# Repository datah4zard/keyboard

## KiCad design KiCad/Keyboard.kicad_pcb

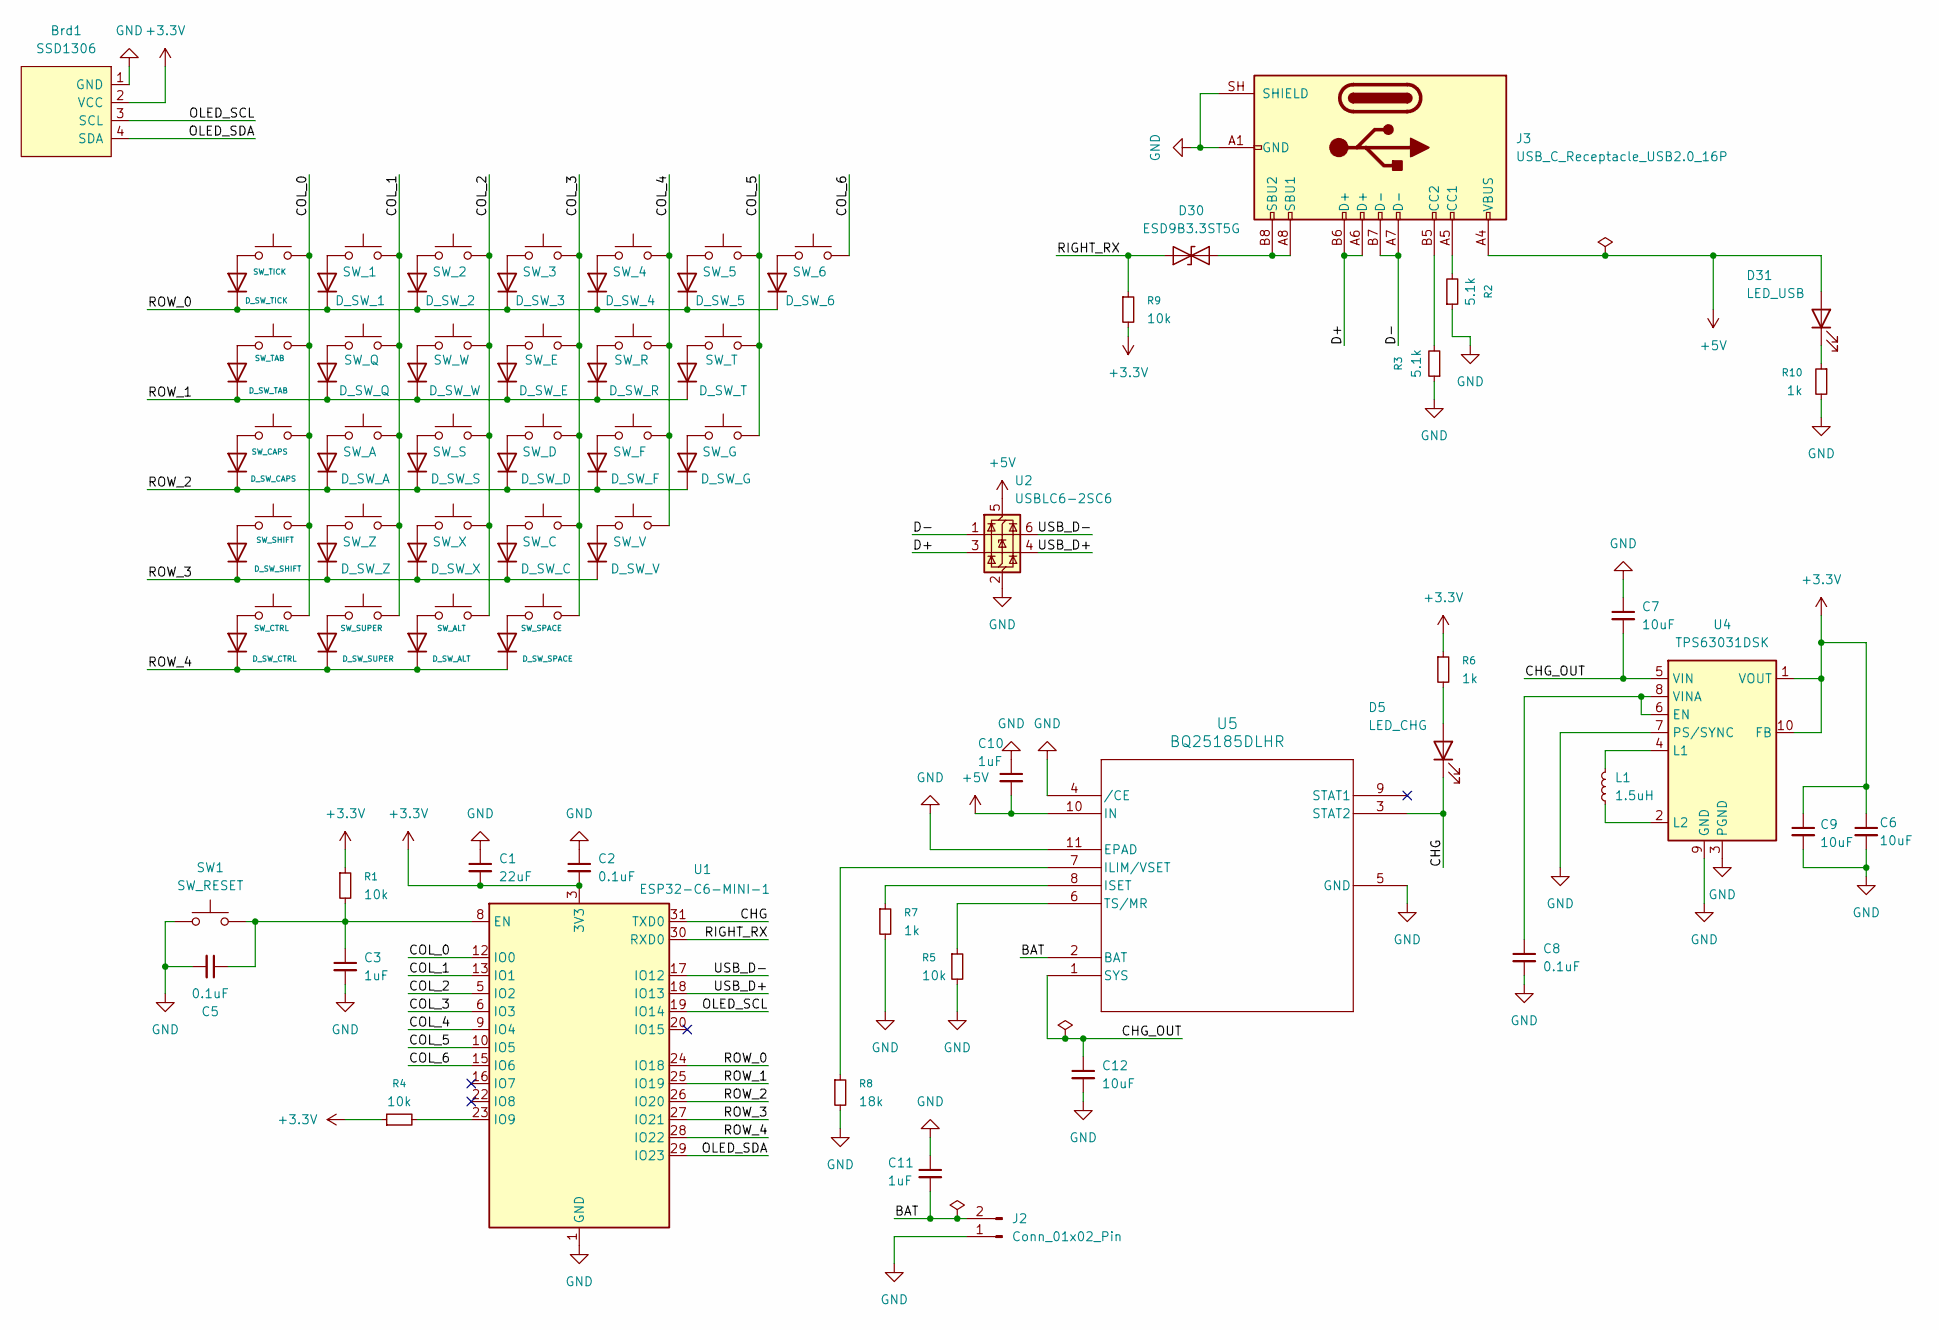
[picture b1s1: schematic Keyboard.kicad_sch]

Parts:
Brd1: SSD1306; 128x64OLED
C1: 22uF; C_0603_1608Metric
C2, C5, C8: 0.1uF; C_0603_1608Metric
C3: 1uF; C_0603_1608Metric
C6, C7, C9: 10uF; C_0603_1608Metric
C10, C11: 1uF; C_0402_1005Metric
C12: 10uF; C_0402_1005Metric
D1: D_SW_TICK; D_SOD-123
D2: D_SW_TAB; D_SOD-123
D3: D_SW_CAPS; D_SOD-123
D4: D_SW_SHIFT; D_SOD-123
D5: LED_CHG; LED_0805_2012Metric
D6: D_SW_CTRL; D_SOD-123
D7: D_SW_1; D_SOD-123
D8: D_SW_Q; D_SOD-123
D9: D_SW_A; D_SOD-123
D10: D_SW_Z; D_SOD-123
D11: D_SW_SUPER; D_SOD-123
D12: D_SW_2; D_SOD-123
D13: D_SW_W; D_SOD-123
D14: D_SW_S; D_SOD-123
D15: D_SW_X; D_SOD-123
D16: D_SW_ALT; D_SOD-123
D17: D_SW_3; D_SOD-123
D18: D_SW_E; D_SOD-123
D19: D_SW_D; D_SOD-123
D20: D_SW_C; D_SOD-123
D21: D_SW_SPACE; D_SOD-123
D22: D_SW_4; D_SOD-123
D23: D_SW_R; D_SOD-123
D24: D_SW_F; D_SOD-123
D25: D_SW_V; D_SOD-123
D26: D_SW_5; D_SOD-123
D27: D_SW_T; D_SOD-123
D28: D_SW_G; D_SOD-123
D29: D_SW_6; D_SOD-123
D30: ESD9B3.3ST5G; D_SOD-923
D31: LED_USB; LED_0805_2012Metric
J2: Conn_01x02_Pin; JST_PH_S2B-PH-SM4-TB_1x02-1MP_P2.00mm_Horizontal
J3: USB_C_Receptacle_USB2.0_16P; USB_C_Receptacle_JAE_DX07S016JA1R1500
L1: 1.5uH; L_Coilcraft_LPS3010
R1, R4, R5, R9: 10k; R_0603_1608Metric
R2, R3: 5.1k; R_0603_1608Metric
R6, R10: 1k; R_0603_1608Metric
R7: 1k; R_0402_1005Metric
R8: 18k; R_0402_1005Metric
SW1: SW_RESET; SW_SPDT_CK_JS102011SAQN
SW2: SW_TICK; SW_Hotswap_Kailh_MX_1.00u
SW3: SW_TAB; SW_Hotswap_Kailh_MX_1.50u
SW4: SW_CAPS; SW_Hotswap_Kailh_MX_1.75u
SW5: SW_SHIFT; SW_Hotswap_Kailh_MX_2.25u
SW6: SW_CTRL; SW_Hotswap_Kailh_MX_1.25u
SW7: SW_1; SW_Hotswap_Kailh_MX_1.00u
SW8: SW_Q; SW_Hotswap_Kailh_MX_1.00u
SW9: SW_A; SW_Hotswap_Kailh_MX_1.00u
SW10: SW_Z; SW_Hotswap_Kailh_MX_1.00u
SW11: SW_SUPER; SW_Hotswap_Kailh_MX_1.25u
SW12: SW_2; SW_Hotswap_Kailh_MX_1.00u
SW13: SW_W; SW_Hotswap_Kailh_MX_1.00u
SW14: SW_S; SW_Hotswap_Kailh_MX_1.00u
SW15: SW_X; SW_Hotswap_Kailh_MX_1.00u
SW16: SW_ALT; SW_Hotswap_Kailh_MX_1.25u
SW17: SW_3; SW_Hotswap_Kailh_MX_1.00u
SW18: SW_E; SW_Hotswap_Kailh_MX_1.00u
SW19: SW_D; SW_Hotswap_Kailh_MX_1.00u
SW20: SW_C; SW_Hotswap_Kailh_MX_1.00u
SW21: SW_SPACE; SW_Hotswap_Kailh_MX_3.00u
SW22: SW_4; SW_Hotswap_Kailh_MX_1.00u
SW23: SW_R; SW_Hotswap_Kailh_MX_1.00u
SW24: SW_F; SW_Hotswap_Kailh_MX_1.00u
SW25: SW_V; SW_Hotswap_Kailh_MX_1.00u
SW26: SW_5; SW_Hotswap_Kailh_MX_1.00u
SW27: SW_T; SW_Hotswap_Kailh_MX_1.00u
SW28: SW_G; SW_Hotswap_Kailh_MX_1.00u
SW29: SW_6; SW_Hotswap_Kailh_MX_1.00u
U1: ESP32-C6-MINI-1
U2: USBLC6-2SC6; SOT-23-6
U4: TPS63031DSK; WSON-10-1EP_2.5x2.5mm_P0.5mm_EP1.2x2mm
U5: BQ25185DLHR; WSON10_DLH_TEX

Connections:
+3.3V: Brd1.2 (VCC), C1.2, C2.2, C6.1, C9.1, R1.1, R4.1, R6.1, R9.2, U1.3 (3V3), U4.1 (VOUT), U4.10 (FB)
+5V: C10.2, D31.2 (A), J3.A4 (VBUS), J3.A9 (VBUS), J3.B4 (VBUS), J3.B9 (VBUS), U2.5 (VBUS), U5.10 (IN)
/BAT: C11.2, J2.2, U5.2 (BAT)
/CHG: D5.1 (K), U1.31 (TXD0), U5.3 (STAT2)
/CHG_OUT: C7.2, C12.1, U4.5 (VIN), U5.1 (SYS)
/COL_0: SW2.2, SW3.2, SW4.2, SW5.2, SW6.2, U1.12 (IO0)
/COL_1: SW7.2, SW8.2, SW9.2, SW10.2, SW11.2, U1.13 (IO1)
/COL_2: SW12.2, SW13.2, SW14.2, SW15.2, SW16.2, U1.5 (IO2)
/COL_3: SW17.2, SW18.2, SW19.2, SW20.2, SW21.2, U1.6 (IO3)
/COL_4: SW22.2, SW23.2, SW24.2, SW25.2, U1.9 (IO4)
/COL_5: SW26.2, SW27.2, SW28.2, U1.10 (IO5)
/COL_6: SW29.2, U1.15 (IO6)
/D+: J3.A6 (D+), J3.B6 (D+), U2.3 (I/O2)
/D-: J3.A7 (D-), J3.B7 (D-), U2.1 (I/O1)
/OLED_SCL: Brd1.3 (SCL), U1.19 (IO14)
/OLED_SDA: Brd1.4 (SDA), U1.29 (IO23)
/RIGHT_RX: D30.1 (A1), R9.1, U1.30 (RXD0)
/ROW_0: D1.1 (K), D7.1 (K), D12.1 (K), D17.1 (K), D22.1 (K), D26.1 (K), D29.1 (K), U1.24 (IO18)
/ROW_1: D2.1 (K), D8.1 (K), D13.1 (K), D18.1 (K), D23.1 (K), D27.1 (K), U1.25 (IO19)
/ROW_2: D3.1 (K), D9.1 (K), D14.1 (K), D19.1 (K), D24.1 (K), D28.1 (K), U1.26 (IO20)
/ROW_3: D4.1 (K), D10.1 (K), D15.1 (K), D20.1 (K), D25.1 (K), U1.27 (IO21)
/ROW_4: D6.1 (K), D11.1 (K), D16.1 (K), D21.1 (K), U1.28 (IO22)
/USB_D+: U1.18 (IO13), U2.4 (I/O2)
/USB_D-: U1.17 (IO12), U2.6 (I/O1)
GND: Brd1.1 (GND), C1.1, C2.1, C3.2, C5.2, C6.2, C7.1, C8.2, C9.2, C10.1, C11.1, C12.2, J2.1, J3.A1 (GND), J3.A12 (GND), J3.B1 (GND), J3.B12 (GND), J3.SH (SHIELD), R2.1, R3.1, R5.2, R7.2, R8.2, R10.2, SW1.1, U1.1 (GND), U1.2 (GND), U1.11 (GND), U1.14 (GND), U1.36 (GND), U1.37 (GND), U1.38 (GND), U1.39 (GND), U1.40 (GND), U1.41 (GND), U1.42 (GND), U1.43 (GND), U1.44 (GND), U1.45 (GND), U1.46 (GND), U1.47 (GND), U1.48 (GND), U1.49 (GND), U1.50 (GND), U1.51 (GND), U1.52 (GND), U1.53 (GND), U2.2 (GND), U4.3 (PGND), U4.7 (PS/SYNC), U4.9 (GND), U4.11 (PGND), U5.4 (/CE), U5.5 (GND), U5.11 (EPAD)
unnamed: D1.2 (A), SW2.1
unnamed: D2.2 (A), SW3.1
unnamed: D3.2 (A), SW4.1
unnamed: D4.2 (A), SW5.1
unnamed: D5.2 (A), R6.2
unnamed: D6.2 (A), SW6.1
unnamed: D7.2 (A), SW7.1
unnamed: D8.2 (A), SW8.1
unnamed: D9.2 (A), SW9.1
unnamed: D10.2 (A), SW10.1
unnamed: D11.2 (A), SW11.1
unnamed: D12.2 (A), SW12.1
unnamed: D13.2 (A), SW13.1
unnamed: D14.2 (A), SW14.1
unnamed: D15.2 (A), SW15.1
unnamed: D16.2 (A), SW16.1
unnamed: D17.2 (A), SW17.1
unnamed: D18.2 (A), SW18.1
unnamed: D19.2 (A), SW19.1
unnamed: D20.2 (A), SW20.1
unnamed: D21.2 (A), SW21.1
unnamed: D22.2 (A), SW22.1
unnamed: D23.2 (A), SW23.1
unnamed: D24.2 (A), SW24.1
unnamed: D25.2 (A), SW25.1
unnamed: D26.2 (A), SW26.1
unnamed: D27.2 (A), SW27.1
unnamed: D28.2 (A), SW28.1
unnamed: D29.2 (A), SW29.1
unnamed: D30.2 (A2), J3.A8 (SBU1), J3.B8 (SBU2)
unnamed: D31.1 (K), R10.1
unnamed: J3.A5 (CC1), R2.2
unnamed: J3.B5 (CC2), R3.2
unnamed: C3.1, C5.1, R1.2, SW1.2, U1.8 (EN)
unnamed: R4.2, U1.23 (IO9)
unnamed: C8.1, U4.6 (EN), U4.8 (VINA)
unnamed: L1.2, U4.4 (L1)
unnamed: L1.1, U4.2 (L2)
unnamed: R8.1, U5.7 (ILIM/VSET)
unnamed: R7.1, U5.8 (ISET)
unnamed: R5.1, U5.6 (TS/MR)

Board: 2 copper layers, 89 parts (0 on the bottom side), 66 nets, no tracks yet.
